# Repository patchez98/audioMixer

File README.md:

# audioMixer (WIP)
Active audio mixer with powerful headphone amp. Current iteration is for 2 analog inputs, 1 output, but future plans include an integrated USB DAC and microphone feedback.

# Features
- Gain knobs for each channel
- Trimpot for setting max gain (necessary for decent volume control on easy-to-drive headphones)
- Capable of driving 600 ohm headphones

# Current Progress
- Built up a v0 board, here's the issues:
-- Input volume control is backwards, so the volume control is pretty bad. Primary gain control seems to work fine.
-- Multiple inputs causes various bad noises
--- This is probably some sort of ground loop issue, since I have 3 ground connections back to the PC. Next revision will have some options to disconnect grounds from jacks to see if that helps.
--- More power input filtering might help as well.
-- It doesn't seem to really drive my HD600s any better than my Fiio BTR3k, at least not in a way I can notice
--- I'm gonna have to add a proper +- 12V supply and use a much stronger opamp next time to see if that helps

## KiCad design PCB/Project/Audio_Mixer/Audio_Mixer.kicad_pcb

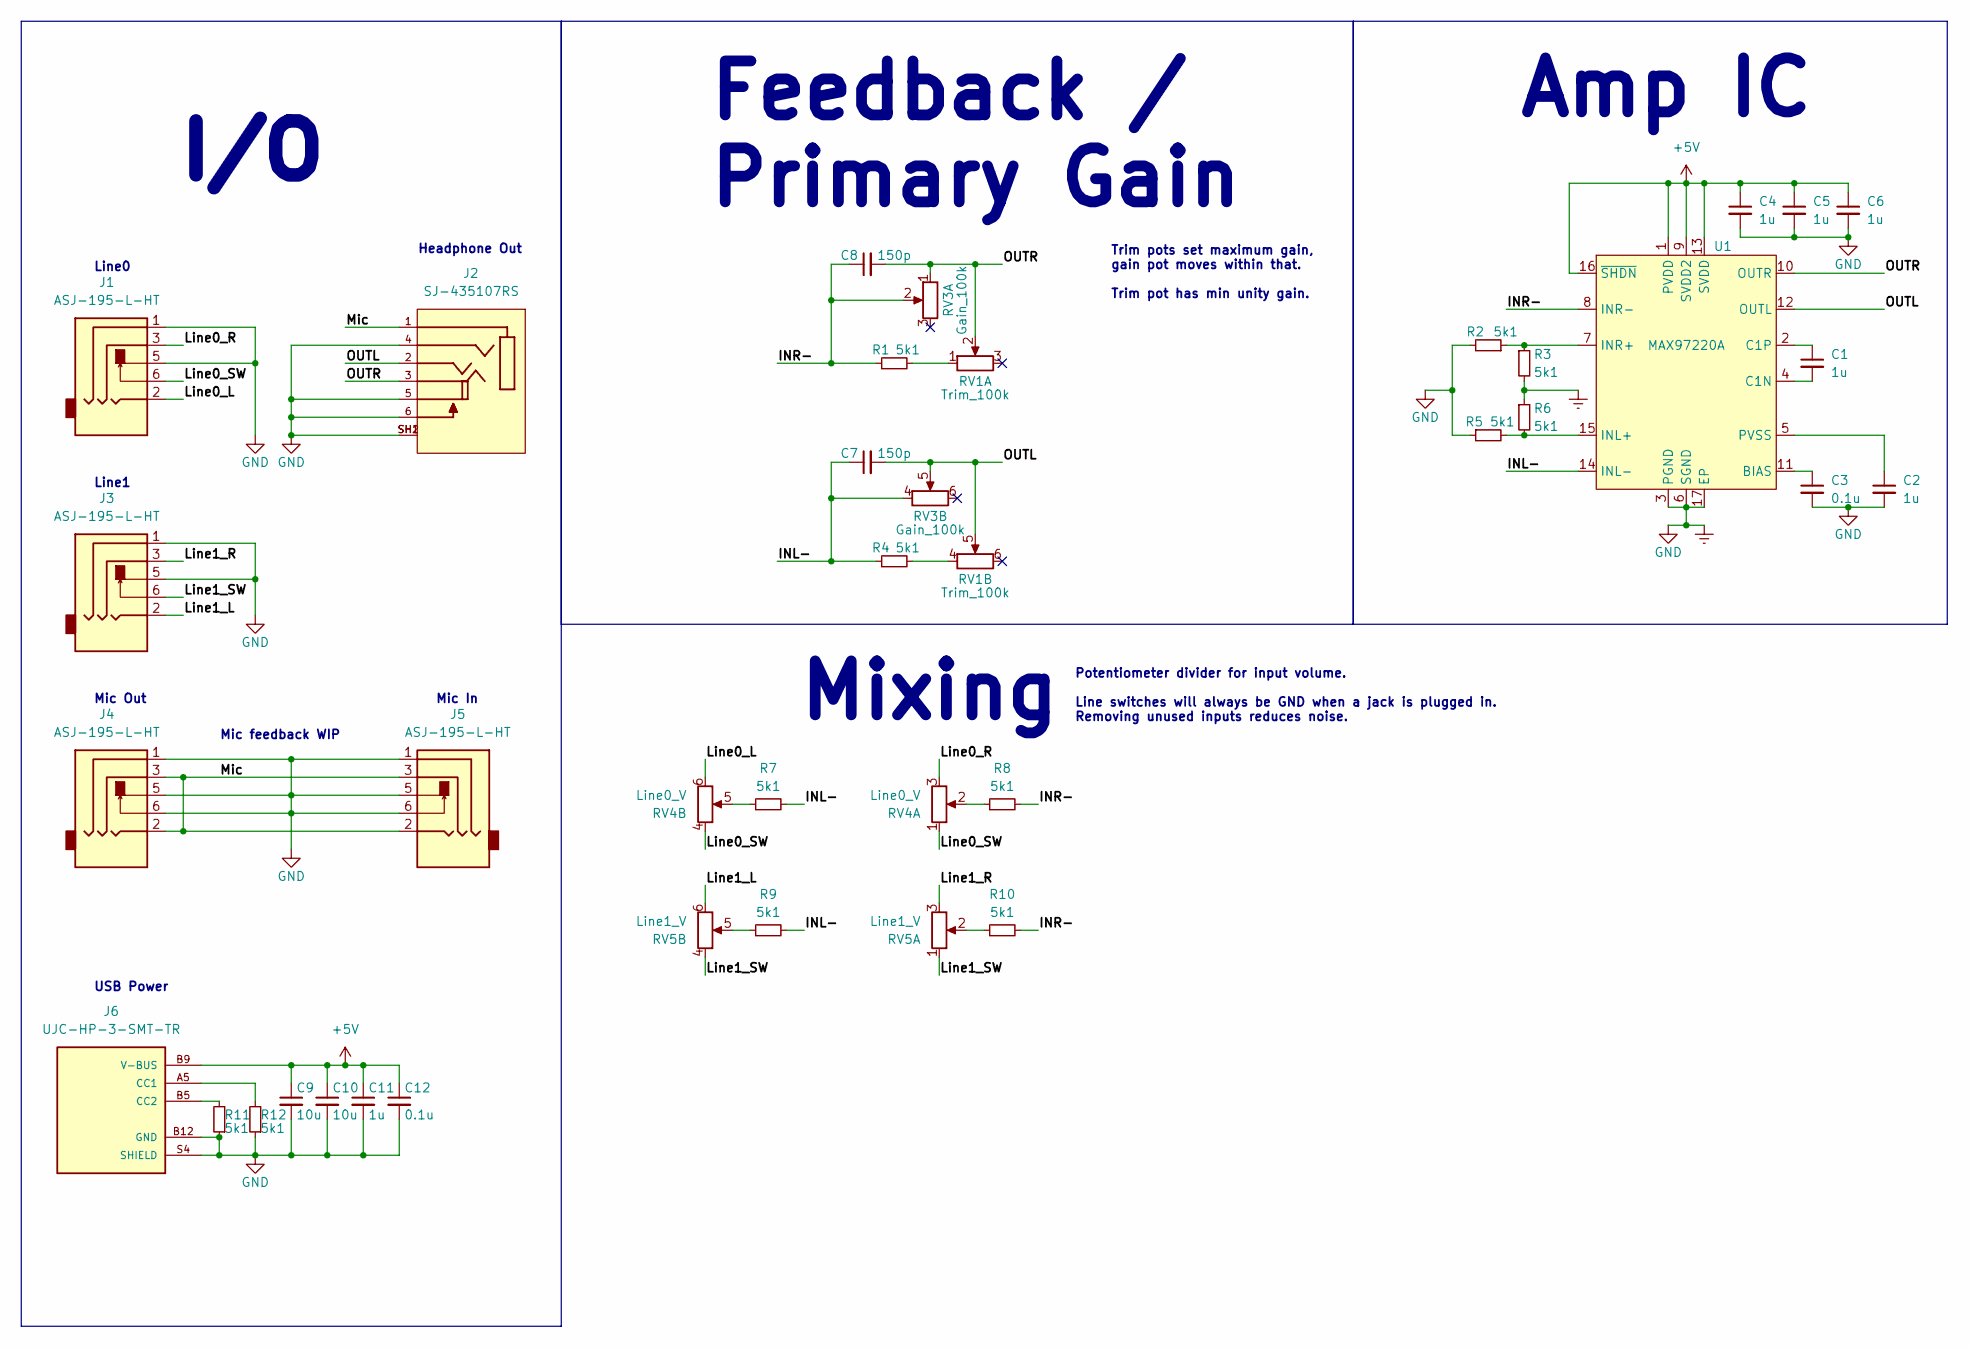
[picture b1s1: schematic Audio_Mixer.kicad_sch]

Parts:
C1, C2, C4, C5, C6, C11: 1u; C_0603_1608Metric
C3: 0.1u; C_0402_1005Metric
C7, C8: 150p; C_0402_1005Metric
C9, C10: 10u; C_0603_1608Metric
C12: 0.1u; C_0603_1608Metric
J1, J3, J4, J5: ASJ-195-L-HT; ASJ-195-X-HT
J2: SJ-435107RS; SJ-435107
J6: UJC-HP-3-SMT-TR; UJC-HP-3-SMT
R1, R2, R3, R4, R5, R6, R7, R8, R9, R10, R11, R12: 5k1; R_0402_1005Metric
RV1: Trim_100k; PS30-2
RV3: Gain_100k; RK14K124
RV4: Line0_V; RK14K124
RV5: Line1_V; RK14K124
U1: MAX97220A; TQFN-16-1EP_3x3mm_P0.5mm_EP1.23x1.23mm_ThermalVias

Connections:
+5V: C4.1, C5.1, C6.1, C9.1, C10.1, C11.1, C12.1, J6.A9 (V-BUS), J6.B9 (V-BUS), U1.1 (PVDD), U1.9 (SVDD2), U1.13 (SVDD), U1.16 (~SHDN)
/INL-: C7.1, R4.1, R7.2, R9.2, RV3.4, U1.14 (INL-)
/INR-: C8.1, R1.1, R8.2, R10.2, RV3.2, U1.8 (INR-)
/Line0_L: J1.2, RV4.6
/Line0_R: J1.3, RV4.3
/Line0_SW: J1.6, RV4.1, RV4.4
/Line1_L: J3.2, RV5.6
/Line1_R: J3.3, RV5.3
/Line1_SW: J3.6, RV5.1, RV5.4
/Mic: J2.1, J4.2, J4.3, J5.2, J5.3
/OUTL: C7.2, J2.2, RV1.5, RV3.5, U1.12 (OUTL)
/OUTR: C8.2, J2.3, RV1.2, RV3.1, U1.10 (OUTR)
Earth: C2.2, C3.2, C4.2, C5.2, C6.2, C9.2, C10.2, C11.2, C12.2, J1.1, J1.5, J2.4, J2.5, J2.6, J2.SH1, J2.SH2, J3.1, J3.5, J4.1, J4.5, J4.6, J5.1, J5.5, J5.6, J6.A12 (GND), J6.B12 (GND), J6.S1 (SHIELD), J6.S2 (SHIELD), J6.S3 (SHIELD), J6.S4 (SHIELD), R2.2, R3.2, R5.1, R6.1, R11.1, R12.1, U1.3 (PGND), U1.6 (SGND), U1.17 (EP)
unnamed: J6.A5 (CC1), R12.2
unnamed: J6.B5 (CC2), R11.2
unnamed: R1.2, RV1.1
unnamed: R4.2, RV1.4
unnamed: R7.1, RV4.5
unnamed: R8.1, RV4.2
unnamed: R9.1, RV5.5
unnamed: R10.1, RV5.2
unnamed: C3.1, U1.11 (BIAS)
unnamed: C1.2, U1.4 (C1N)
unnamed: C1.1, U1.2 (C1P)
unnamed: R5.2, R6.2, U1.15 (INL+)
unnamed: R2.1, R3.1, U1.7 (INR+)
unnamed: C2.1, U1.5 (PVSS)

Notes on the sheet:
Feedback / Primary Gain
Mixing
Trim pots set maximum gain, gain pot moves within that. Trim pot has min unity gain.
I/O
Headphone Out
Mic In
Mic feedback WIP
Amp IC
Line0
Potentiometer divider for input volume. Line switches will always be GND when a jack is plugged in. Removing unused inputs reduces noise.
Line1
Mic Out
USB Power

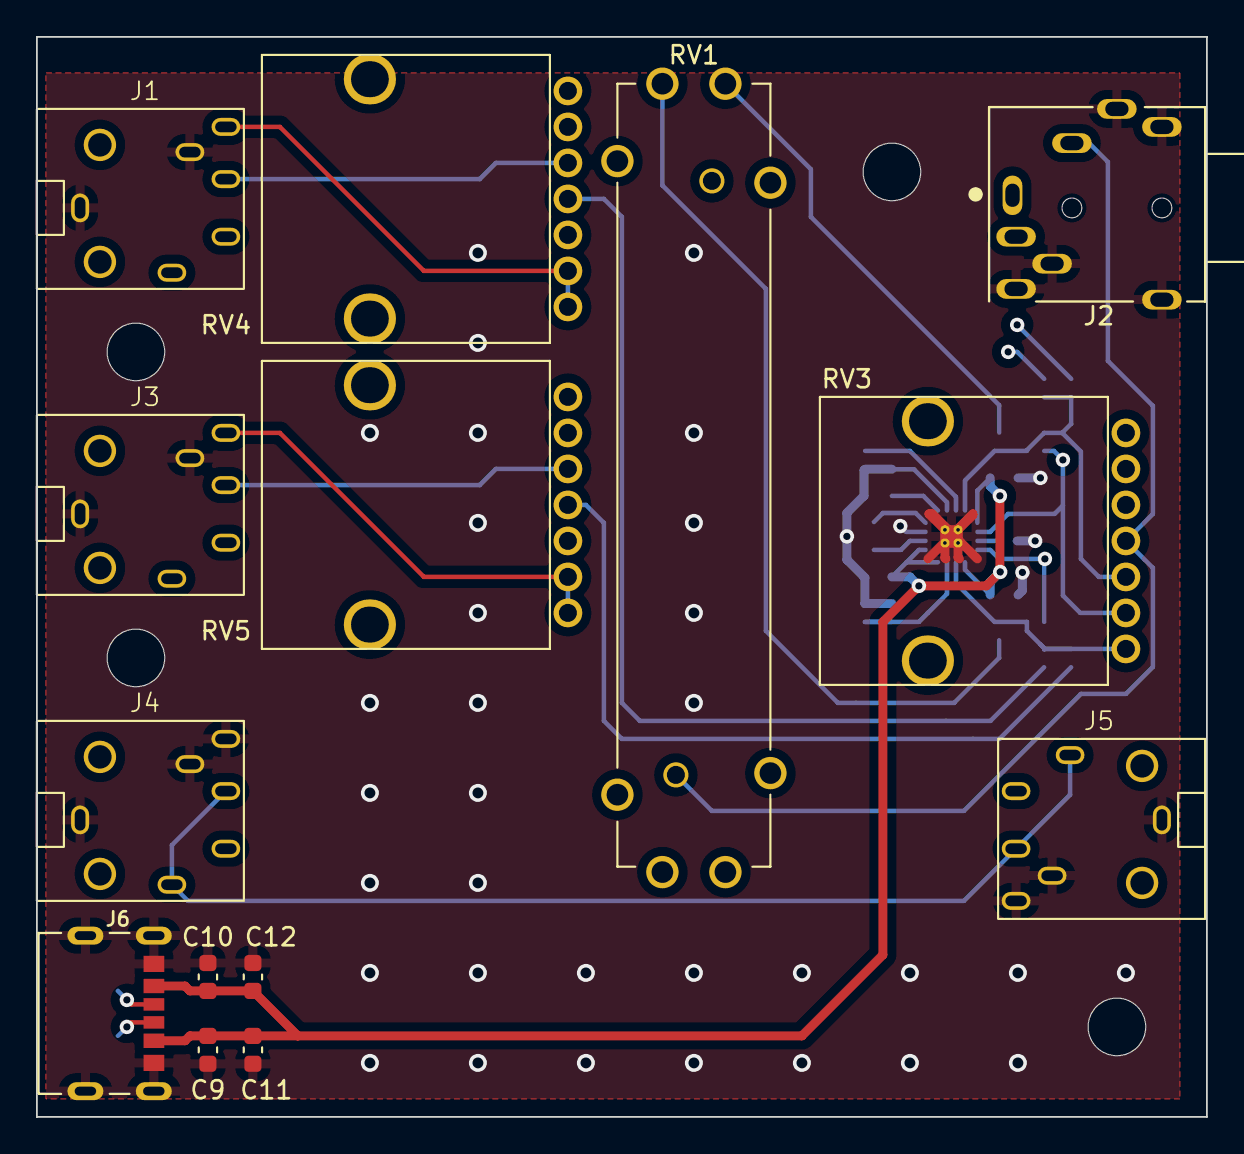
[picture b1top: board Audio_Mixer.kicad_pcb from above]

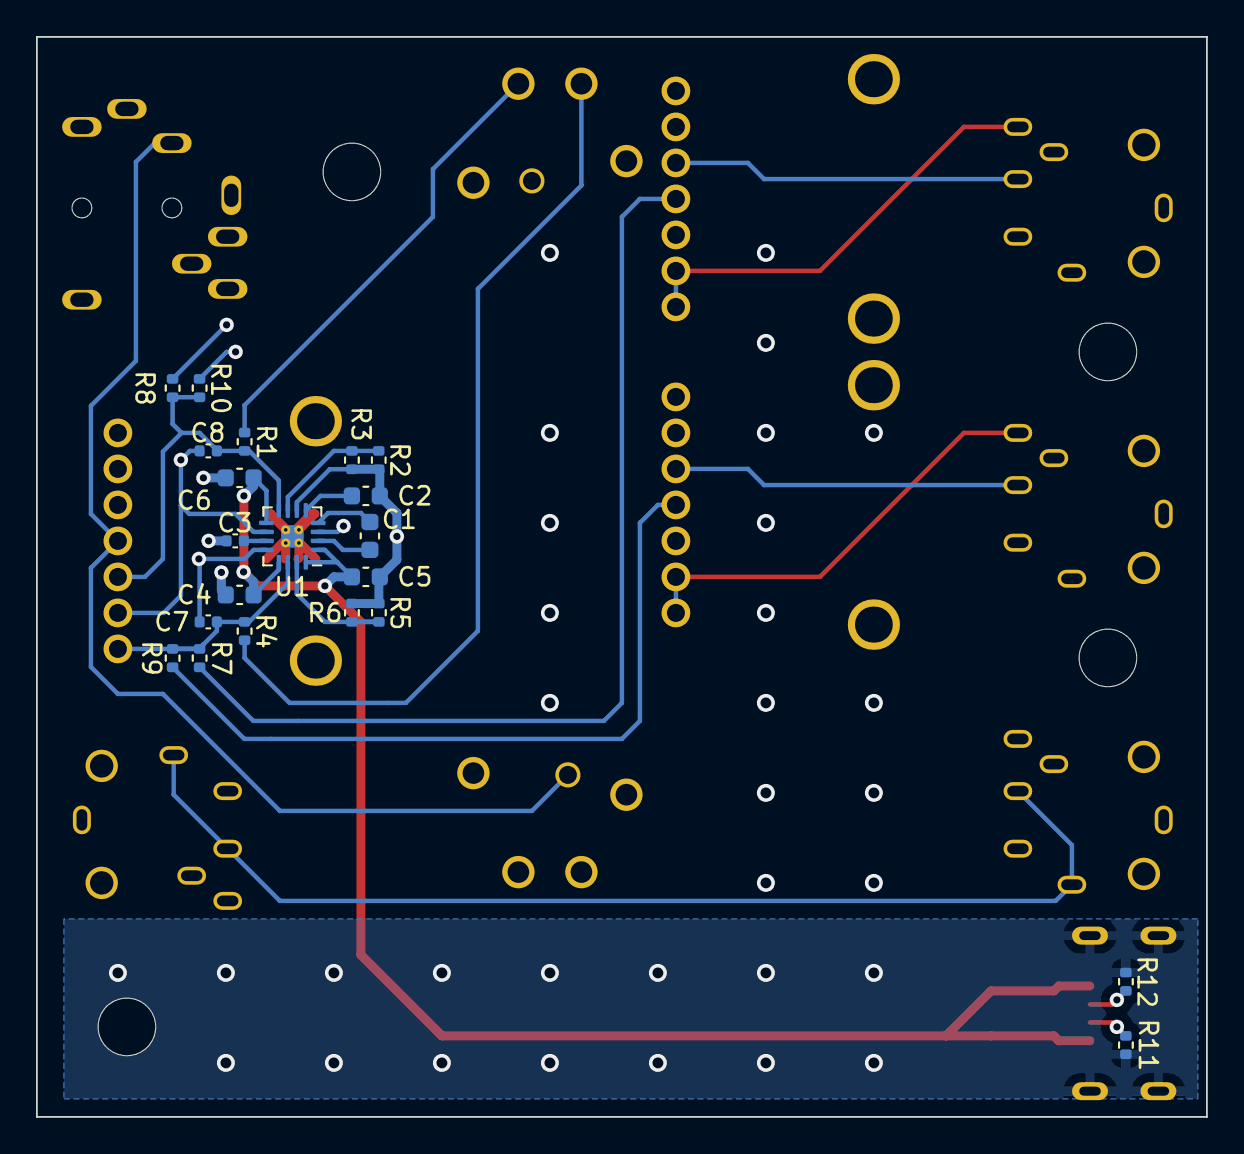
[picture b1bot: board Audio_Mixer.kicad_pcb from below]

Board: 4 copper layers, 65.0 x 60.0 mm, 35 parts (21 on the bottom side), 27 nets.

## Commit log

2023-09-16 Started work on project. Schematic mostly done for v0.
2023-10-12 Boards ordered for v0; gerbs included
